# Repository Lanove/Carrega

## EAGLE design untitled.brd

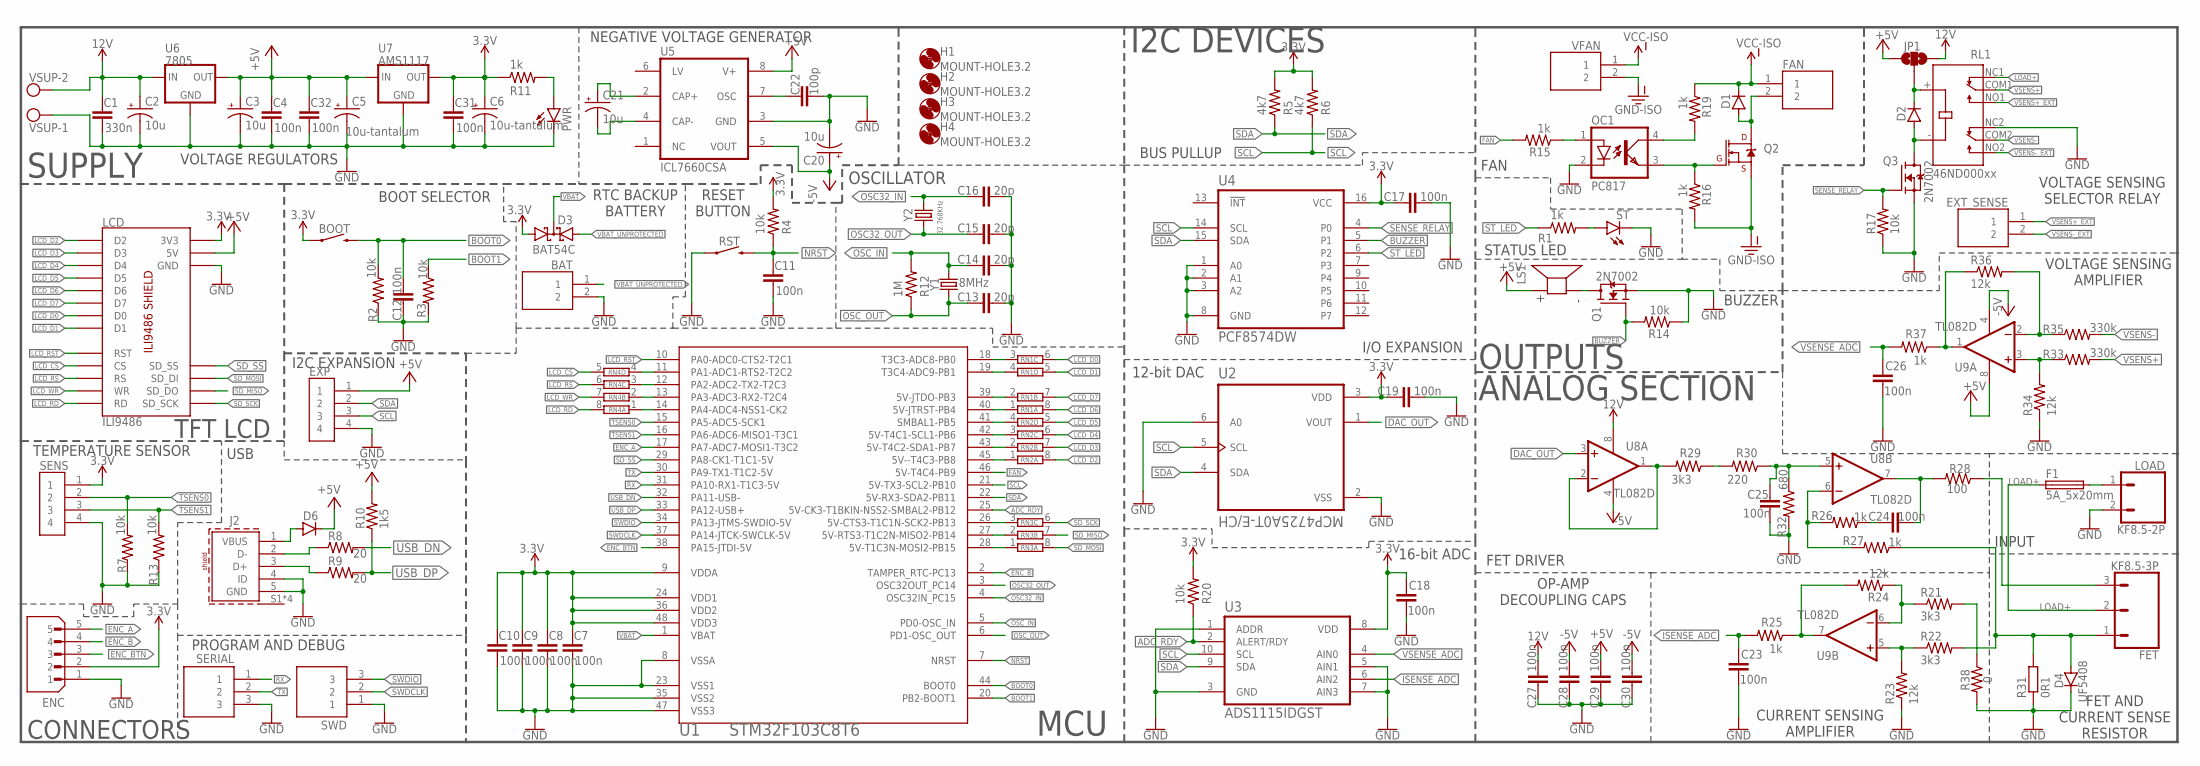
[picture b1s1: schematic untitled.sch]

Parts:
BAT: B2B-XH-A(LF)(SN); JST_B2B-XH-A(LF)(SN)
BOOT: MOMENTARY-SWITCH-SPST-SMD-6.0X3.5MM; TACTILE_SWITCH_SMD_6.0X3.5MM
C1: 330n; C0805
C2, C3, C20, C21: 10u; E2,5-6
C4, C7, C8, C9, C10, C11, C12, C17, C18, C19, C23, C24, C25, C26, C27, C28, C29, C30, C31, C32: 100n; C0805
C5, C6: 10u-tantalum; CT3528
C13, C14, C15, C16: 20p; C0805
C22: 100p; C0805
D1, D2, D6: DIODE-DO-214AC; DO-214AC
D3: BAT54C; SOT23
D4: UF5408; DO201-15
ENC: B5B-XH-A(LF)(SN); JST_B5B-XH-A(LF)(SN)
EXP: JST-XH-4P; JST_B4B-XH-A(LF)(SN)
EXT_SENSE: B2B-XH-A(LF)(SN); JST_B2B-XH-A(LF)(SN)
F1: 5A_5x20mm; FUSE_HOLDER_5X20MM
FAN: B2B-XH-A(LF)(SN); JST_B2B-XH-A(LF)(SN)
FET: KF8.5-3P; KF7.62-3P
H1, H2, H3, H4: MOUNT-HOLE3.2; 3,2
J2: 629105136821
JP1: JUMPER-SMT_3_NO_SILK; SMT-JUMPER_3_NO_SILK
LCD: ILI9486; ILI9486-SHIELD
LOAD: KF8.5-2P; KF7.62
LS1: AI-1223-TWT-12V-R; XDCR_AI-1223-TWT-12V-R
OC1: PC817; DIL04
PWR: LEDCHIP-LED0805; CHIP-LED0805
Q1, Q3: 2N7002; SOT95P240X111-3N
Q2: MOSFET-NCH-FDD8780; TO-252/DPAK
R1, R11, R15, R16, R19, R26, R27: 1k; M0805
R2, R3, R4, R7, R13, R14, R17, R20: 10k; M0805
R5, R6: 4k7; M0805
R8, R9: 20; M0805
R10: 1k5; M0805
R12: 1M; M0805
R21, R22: 3k3; R0603
R23, R24, R34, R36: 12k; R0603
R25, R37: 1k; R0603
R28: 100; M0805
R29: 3k3; M0805
R30: 220; M0805
R31: 0R1; 0922/22
R32: 680; M0805
R33, R35: 330k; R0603
R38: 0; M0805
RL1: 46ND000xx; RELAY_G2RL-2_12DC
RN1, RN2, RN3, RN4: 4R-N0402ARV341; 4X0402ARV341
RST: MOMENTARY-SWITCH-SPST-SMD-6.0X3.5MM; TACTILE_SWITCH_SMD_6.0X3.5MM
SENS: JST-XH-4P; JST_B4B-XH-A(LF)(SN)
SERIAL: B3B-XH-A(LF)(SN); JST_B3B-XH-A(LF)(SN)
ST: LEDCHIP-LED0805; CHIP-LED0805
SWD: B3B-XH-A(LF)(SN); JST_B3B-XH-A(LF)(SN)
U1: STM32F103C8T6; TQFP48
U2: MCP4725A0T-E/CH; SOT95P270X145-6N
U3: ADS1115IDGST; SOP50P490X110-10N
U4: PCF8574DW; SOIC127P1030X265-16N
U5: ICL7660CSA; SO08
U6: 7805; 78XXS
U7: AMS1117; SOT89R
U8, U9: TL082D; SO08
VFAN: B2B-XH-A(LF)(SN); JST_B2B-XH-A(LF)(SN)
VSUP: MKDSN1,5/2-5,08
Y1: 8MHz; HC49US
Y2: 32.768KHz; MC-306

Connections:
3.3V: BOOT.1, C6.+, C7.1, C8.1, C9.1, C10.1, C17.1, C18.1, C19.1, C31.1, D3.1 (A1), ENC.2, LCD.3V3, R4.2, R5.2, R6.2, R11.1, R20.2, SENS.1, U1.9 (VDDA), U1.24 (VDD1), U1.36 (VDD2), U1.48 (VDD3), U2.3 (VDD), U3.8 (VDD), U4.16 (VCC), U7.3 (OUT), U7.4 (OUT)
12V: C1.1, C2.+, C27.2, JP1.3, U6.IN, U8.8 (V+), VSUP.2
+5V: C3.+, C4.1, C5.+, C29.2, C32.1, D6.C, EXP.1, JP1.1, LCD.5V, LS1.P (+), R10.2, U5.8 (V+), U6.OUT, U7.1 (IN), U9.8 (V+)
-5V: C20.+, C28.2, C30.2, U5.5 (VOUT), U8.4 (V-), U9.4 (V-)
ADC_RDY: R20.1, U1.25 (5V-CK3-T1BKIN-NSS2-SMBAL2-PB12), U3.2 (ALERT/RDY)
BOOT0: BOOT.2, C12.1, R2.2, U1.44 (BOOT0)
BOOT1: R3.1, U1.20 (PB2-BOOT1)
BUZZER: Q1.1 (G), R14.2, U4.5 (P1)
DAC_OUT: U2.1 (VOUT), U8.3 (+IN)
ENC_A: ENC.5, U1.17 (PA7-ADC7-MOSI1-T3C2)
ENC_B: ENC.4, U1.2 (TAMPER_RTC-PC13)
ENC_BTN: ENC.3, U1.38 (PA15-JTDI-5V)
FAN: R15.2, U1.46 (5V-T4C4-PB9)
GND: BAT.2, C1.2, C2.-, C3.-, C4.2, C5.-, C6.-, C7.2, C8.2, C9.2, C10.2, C11.2, C12.2, C13.2, C14.2, C15.2, C16.2, C17.2, C18.2, C19.2, C20.-, C22.1, C23.2, C25.1, C26.2, C27.1, C28.1, C29.1, C30.1, C31.2, C32.2, D4.C, ENC.1, EXP.4, J2.4 (ID), J2.5 (GND), LCD.GND, LCD.GND1 (GND), LCD.GND2 (GND), LOAD.2, OC1.2 (C), PWR.C, Q1.2 (S), Q3.2 (S), R2.1, R3.2, R7.1, R13.1, R14.1, R17.1, R23.1, R31.1, R32.2, R34.1, R38.2, RL1.NC2, RST.1, SENS.4, SERIAL.3, ST.C, SWD.1, U1.8 (VSSA), U1.23 (VSS1), U1.35 (VSS2), U1.47 (VSS3), U2.2 (VSS), U2.6 (A0), U3.1 (ADDR), U3.3 (GND), U3.5 (AIN1), U3.7 (AIN3), U4.1 (A0), U4.2 (A1), U4.3 (A2), U4.8 (GND), U5.3 (GND), U6.GND, U7.2 (GND), VSUP.1
GND-ISO: Q2.3 (S), R16.2, VFAN.2
ISENSE_ADC: C23.1, R25.2, U3.6 (AIN2)
LCD_CS: LCD.LCD_CS (CS), RN4.5 (2)
LCD_D0: LCD.LCD_D0 (D0), RN1.6 (2)
LCD_D1: LCD.LCD_D1 (D1), RN1.5 (2)
LCD_D2: LCD.LCD_D2 (D2), RN2.8 (2)
LCD_D3: LCD.LCD_D3 (D3), RN2.7 (2)
LCD_D4: LCD.LCD_D4 (D4), RN2.6 (2)
LCD_D5: LCD.LCD_D5 (D5), RN2.5 (2)
LCD_D6: LCD.LCD_D6 (D6), RN1.8 (2)
LCD_D7: LCD.LCD_D7 (D7), RN1.7 (2)
LCD_RD: LCD.LCD_RD (RD), RN4.8 (2)
LCD_RS: LCD.LCD_RS (RS), RN4.6 (2)
LCD_RST: LCD.LCD_RST (RST), U1.10 (PA0-ADC0-CTS2-T2C1)
LCD_WR: LCD.LCD_WR (WR), RN4.7 (2)
LOAD+: F1.1, FET.2, RL1.NC1
unnamed: LS1.N (-), Q1.3 (D)
unnamed: RN1.3 (1), U1.18 (T3C3-ADC8-PB0)
unnamed: RN1.4 (1), U1.19 (T3C4-ADC9-PB1)
unnamed: PWR.A, R11.2
unnamed: RN1.2 (1), U1.39 (5V-JTDO-PB3)
unnamed: D6.A, J2.1 (VBUS)
unnamed: RN1.1, U1.40 (5V-JTRST-PB4)
unnamed: RN2.4 (1), U1.41 (SMBAL1-PB5)
unnamed: RN2.3 (1), U1.42 (5V-T4C1-SCL1-PB6)
unnamed: RN2.1, U1.45 (5V--T4C3-PB8)
unnamed: RN2.2 (1), U1.43 (5V-T4C2-SDA1-PB7)
unnamed: RN3.3 (1), U1.26 (5V-CTS3-T1C1N-SCK2-PB13)
unnamed: RN3.2 (1), U1.27 (5V-RTS3-T1C2N-MISO2-PB14)
unnamed: RN3.1, U1.28 (5V-T1C3N-MOSI2-PB15)
unnamed: RN4.4 (1), U1.11 (PA1-ADC1-RTS2-T2C2)
unnamed: J2.3 (D+), R9.1
unnamed: RN4.3 (1), U1.12 (PA2-ADC2-TX2-T2C3)
unnamed: J2.2 (D-), R8.1
unnamed: RN4.1, U1.14 (PA4-ADC4-NSS1-CK2)
unnamed: RN4.2 (1), U1.13 (PA3-ADC3-RX2-T2C4)
unnamed: OC1.3 (EMIT), Q2.1 (G), R16.1
unnamed: R1.2, ST.A
unnamed: OC1.1 (A), R15.1
unnamed: D1.A, FAN.2, Q2.2 (D)
unnamed: D2.A, Q3.3 (D), RL1.- (COIL2)
unnamed: OC1.4 (COL), R19.2
unnamed: D2.C, JP1.2, RL1.+ (COIL1)
unnamed: C21.+, U5.2 (CAP+)
unnamed: C21.-, U5.4 (CAP-)
unnamed: F1.2, LOAD.1
unnamed: C22.2, U5.7 (OSC)
unnamed: R33.1, R34.2, U9.3 (+IN)
unnamed: D4.A, FET.1, R22.2, R27.1, R31.2
unnamed: R22.1, R23.2, U9.5 (+IN)
unnamed: R21.1, R24.1, U9.6 (-IN)
unnamed: C24.1, R26.1
unnamed: R24.2, R25.1, U9.7 (OUT)
unnamed: C24.2, R28.2, U8.7 (OUT)
unnamed: C25.2, R30.1, R32.1, U8.5 (+IN)
unnamed: R26.2, R27.2, U8.6 (-IN)
unnamed: FET.3, R28.1
unnamed: R29.1, R30.2
unnamed: R29.2, U8.1 (OUT), U8.2 (-IN)
unnamed: R35.1, R36.2, U9.2 (-IN)
unnamed: R21.2, R38.1
unnamed: R36.1, R37.1, U9.1 (OUT)
NRST: C11.1, R4.1, RST.2, U1.7 (NRST)
OSC32_IN: C16.1, U1.4 (OSC32IN_PC15), Y2.4 (2)
OSC32_OUT: C15.1, U1.3 (OSC32OUT_PC14), Y2.1
OSC_IN: C14.1, R12.2, U1.5 (PD0-OSC_IN), Y1.2
OSC_OUT: C13.1, R12.1, U1.6 (PD1-OSC_OUT), Y1.1
RX: SERIAL.1, U1.31 (PA10-RX1-T1C3-5V)
SCL: EXP.3, R6.1, U1.21 (5V-TX3-SCL2-PB10), U2.5 (SCL), U3.10 (SCL), U4.14 (SCL)
SDA: EXP.2, R5.1, U1.22 (5V-RX3-SDA2-PB11), U2.4 (SDA), U3.9 (SDA), U4.15 (SDA)
SD_MISO: LCD.SD_DO, RN3.7 (2)
SD_MOSI: LCD.SD_DI, RN3.8 (2)
SD_SCK: LCD.SD_SCK, RN3.6 (2)
SD_SS: LCD.SD_SS, U1.29 (PA8-CK1-T1C1-5V)
SENSE_RELAY: Q3.1 (G), R17.2, U4.4 (P0)
ST_LED: R1.1, U4.6 (P2)
SWDCLK: SWD.2, U1.37 (PA14-JTCK-SWCLK-5V)
SWDIO: SWD.3, U1.34 (PA13-JTMS-SWDIO-5V)
TSENS0: R7.2, SENS.2, U1.15 (PA5-ADC5-SCK1)
TSENS1: R13.2, SENS.3, U1.16 (PA6-ADC6-MISO1-T3C1)
TX: SERIAL.2, U1.30 (PA9-TX1-T1C2-5V)
USB_DN: R8.2, U1.32 (PA11-USB-)
USB_DP: R9.2, R10.1, U1.33 (PA12-USB+)
VBAT: D3.3 (CC), U1.1 (VBAT)
VBAT_UNPROTECTED: BAT.1, D3.2 (A2)
VCC-ISO: D1.C, FAN.1, R19.1, VFAN.1
VSENS+: R33.2, RL1.COM1
VSENS+_EXT: EXT_SENSE.1, RL1.NO1
VSENS-: R35.2, RL1.COM2
VSENS-_EXT: EXT_SENSE.2, RL1.NO2
VSENSE_ADC: C26.1, R37.2, U3.4 (AIN0)

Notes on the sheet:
CONNECTORS
TFT LCD
MCU
SUPPLY
I2C DEVICES
OUTPUTS
ANALOG SECTION
OSCILLATOR
RESET BUTTON
RTC BACKUP BATTERY
BOOT SELECTOR
VOLTAGE REGULATORS
NEGATIVE VOLTAGE GENERATOR
I2C EXPANSION
TEMPERATURE SENSOR
USB
PROGRAM AND DEBUG
BUS PULLUP
I/O EXPANSION
16-bit ADC
12-bit DAC
BUZZER
STATUS LED
FAN
VOLTAGE SENSING SELECTOR RELAY
VOLTAGE SENSING AMPLIFIER
INPUT
FET AND CURRENT SENSE RESISTOR
CURRENT SENSING AMPLIFIER
OP-AMP DECOUPLING CAPS
FET DRIVER

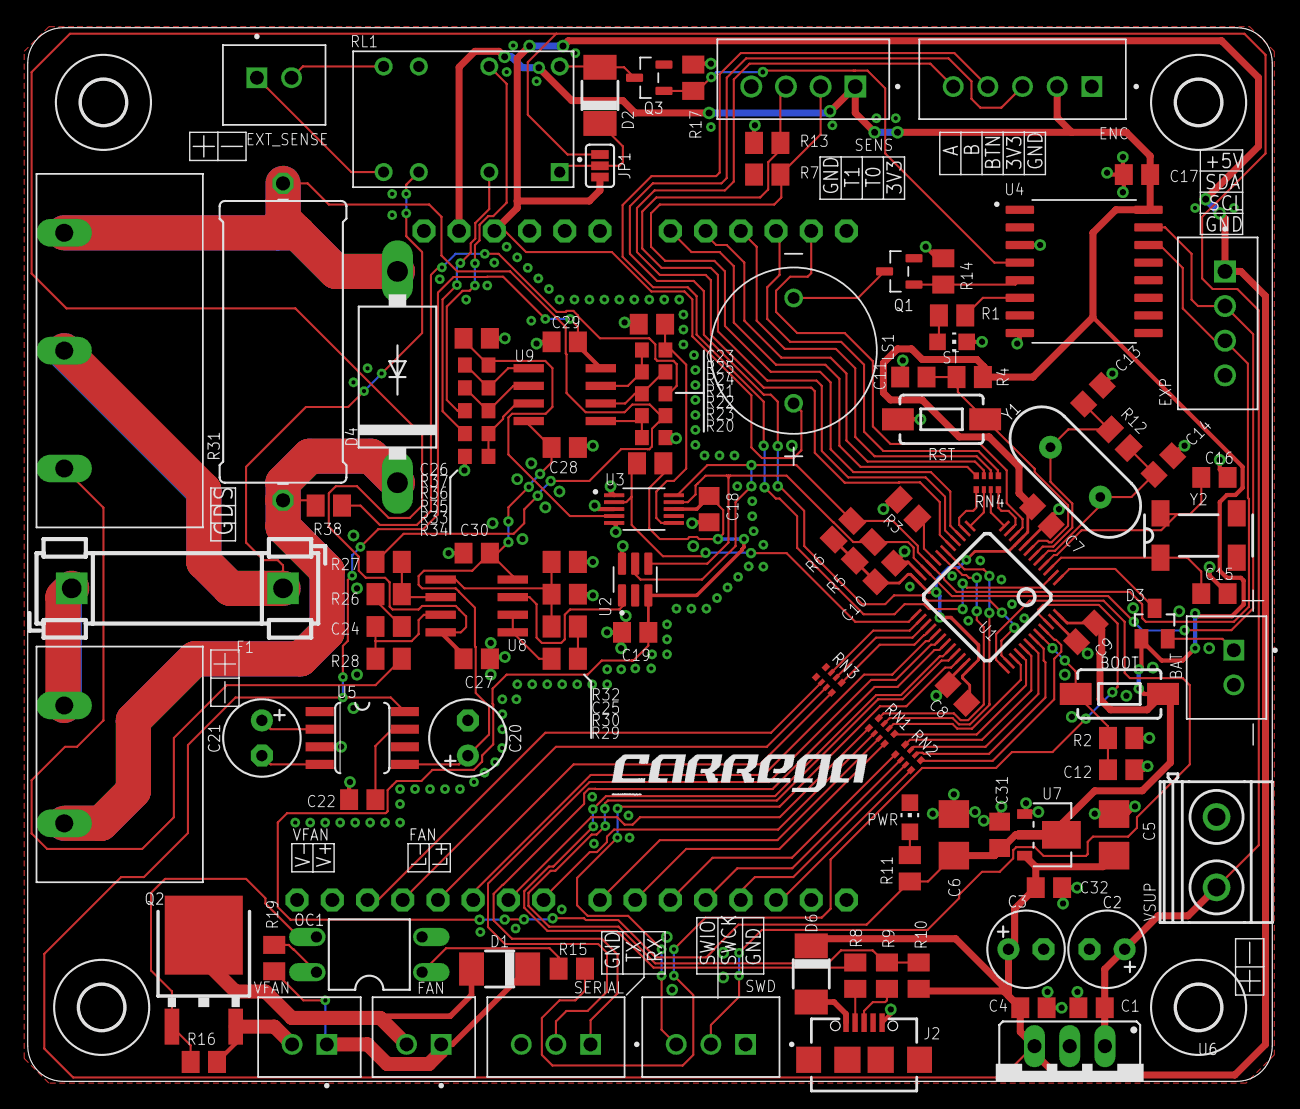
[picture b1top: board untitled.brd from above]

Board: 2 copper layers, 89.8 x 76.0 mm, 119 parts (1 on the bottom side), 105 nets.

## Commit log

2022-03-29 Init

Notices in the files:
parts and their libraries:
SparkFun-Switches: Licensing: Creative Commons ShareAlike 4.0 International - https://creativecommons.org/licenses/by-sa/4.0
Wurth_Connectors_WR-USB: Copyright: Würth Elektronik
